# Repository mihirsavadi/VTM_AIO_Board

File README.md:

# All-in-One Board | Virginia Tech Motorsports

This repository contains all documentation and material related to [Virginia Tech's Formula SAE team - Virginia Tech Motorsports](https://vtmotorsports.weebly.com/) - All-in-One board for our 2021/2022 internal combustion vehicle.

The AIO board encapsulates several data acquisition features, as well as rules compliant power staging and power distribution, into a single PCB. Note that it is tightly integrated with our Brake-System-Plausibility device which can be found at the repository over [here](https://vtmotorsports.weebly.com/). 

The repository is split into [hardware](./hardware) and [software](./software) subdirectories. The former contains schematics, BOM, etc. Note that I used Diptrace as my PCB design software of choice, and while all critical files for board fabrication/inventory management are available in standard formats (GERBER, pdf's, spreadsheets), the original Diptrace files are included as well. The rest of the team uses Altium, however I prefer Diptrace - its easy to port between the two. The software directory contains Platform-IO project files that run both the MAIN and DRS microcontrollers on the AIO board. Custom Hardware Abstraction Layers/API's were made in order to make it easy to work with the board's slew of features. Both subdirectories include folders containing all our old revisions, which can be safely ignored unless you are a VTM member and/or are curious about the evolution of our design process.  

Running our microcontrollers with the Arduino bootloader and its general hardware abstraction layer not only allows us access to a vast array of arduino compatible easy-to-use libraries for various embedded hardware components (saving us dev time), but also allows lesser experienced team members to absorb functionality and hit the ground running with contribution quicker. We suffer from little to nothing when it comes to the typical drawbacks of using the arduino abstraction layer because 1. we are using proven and optimized hardware by standardizing to the teensy line of microcontrollers, 2. we are not using the stock arduino IDE, rather platform IO which is an extremely rich and ever-expanding IDE for a vast array of embedded processors and development boards, allowing us to easily and reliably integrate custom as well as off-the-shelf open source libraries, and 3. all of our applications are low speed and low memory.  

## Software Guide

Please read all the code in the /src directories for both the AIO_MAIN_MCU and AIO_DRS_MCU to understand the system thoroughly and before attempting to modify any code. All pin/IO definitions for the microcontrollers are established as macros in a file called "pin_definitions.hpp" in both directories, please study these and compare them with the schematics in the hardware subdirectories. Only use these macros for pin control in the code in order to keep things consistent, clean, and less error prone. Also remember to see header comments in order to match code and hardware compatibility - everything in the top level directories by default should be compatible with the latest hardware revision, which as of writing this is 'DAQ_PDU AIO BOARD REV2'.

In order to get an idea of how to use the various libraries to interact with peripherals on the AIO (SD card, GPS, IMU), read the documentation and example arduino sketches in the lib_dep directory. So for the MAIN MCU this would be [.pio\libdeps\teensy35](./software/AIO_MAIN_MCU/.pio/libdeps/teensy35)

If you want to add libraries, please visit the Platform-IO libraries registry and add the dependency into our project's 'platformio.ini' file. [This video](https://www.youtube.com/watch?v=buFKeqbafDI) illustrates this nicely. This file basically configures every option about our project - the serial port baud rate, library dependencies, what board etc were using, everything. Its a very powerful tool.  

Note that the arduino hardware abstraction layer compiles C++, but in reality most things are in C. The only significant usable C++ features are classes. Absolutely nothing from the C++ standard library should be used as it will wreck your boards memory and probably cause stack fragmentation which will either brick or freeze your board, which will be hard to debug. You can get away with using an std::string or an std::vector here or there but since its such a nasty slippery slope that hits quick stay away from it at all costs. So if you want to use convenient C++ like data structures (besides classes or structs) I recommend you don't. If you feel like you really must then its a sign your code is probably a tad too complicated for a simple embedded application such as ours - it might even mean you may be compromising on execution speed, which is bad given the primary purpose of software in this system being for data logging. [This](https://apprize.best/programming/arduino/10.html) is a nice resource regarding arduino programming and data structures.

I've tried my best to comment as much as possible, but if you have any questions reach out to me at mihirsavadi1@vt.edu.

## TODOS and Notes

- Add more pictures of the board to this readme, assembled as well as in enclosure (include wire jumps on the back)
- Implement BB method in DRS MCU class
- Implement IMU and GPS integration into the [aioMainMCU class](software/AIO_MAIN_MCU/src/aioMainMCU.cpp) (*integrated, not yet tested in hardware)
- Use RTC in GPS to get time data and add as a data point to CSV logging - IMPORTANT!
- Implement UART comms between DRS and MAIN MCU's
- Sort out CANBUS in MAIN MCU
- Clean up old revision subdirectories with information regarding what went wrong with them
- Include links to lecture videos describing entire system that we made (to youtube or something)
- Include wire map information here when that is all finalized and hashed out. 
- Add the CAD models for the AIO enclosure + BOM. Add a little window for a tiny fan for cooling, embedded flush into the enclosure.
- Add link to AIO breakdown documentation video

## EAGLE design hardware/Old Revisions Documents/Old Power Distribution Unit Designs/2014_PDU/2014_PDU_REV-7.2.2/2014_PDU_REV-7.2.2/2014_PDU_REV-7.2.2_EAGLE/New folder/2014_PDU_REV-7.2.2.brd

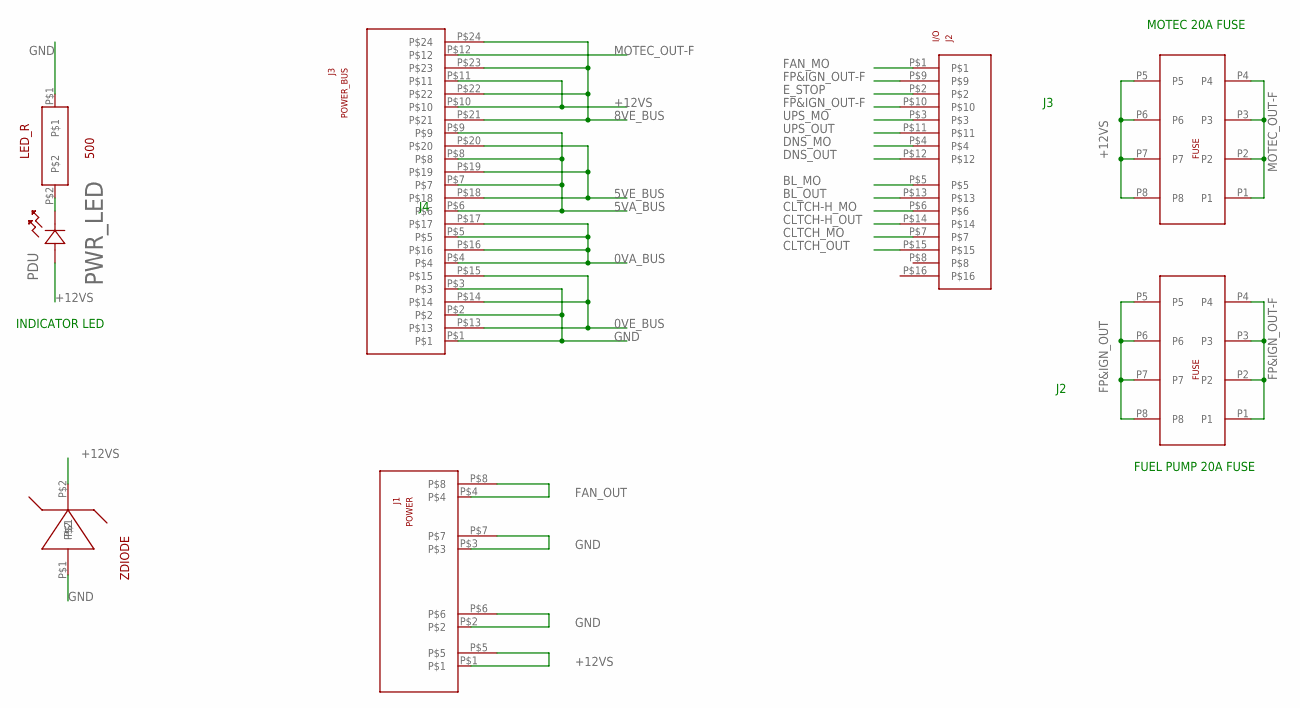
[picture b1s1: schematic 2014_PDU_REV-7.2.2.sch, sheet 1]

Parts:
I/O: J2; 39-30-1160
LED_R: 500; CRCW_2010_390R_JNEF
PDU: PWR_LED; LED_597-3111-407F
POWER: J1; 42820-4223
POWER_BUS: J3; 39-30-1240
U$1, U$2: 178.6165.0002
ZDIODE: DDZ20C-7

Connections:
0VA_BUS: POWER_BUS.P$4, POWER_BUS.P$5, POWER_BUS.P$16, POWER_BUS.P$17
0VE_BUS: POWER_BUS.P$13, POWER_BUS.P$14, POWER_BUS.P$15
5VA_BUS: POWER_BUS.P$6, POWER_BUS.P$7, POWER_BUS.P$8, POWER_BUS.P$9
5VE_BUS: POWER_BUS.P$18, POWER_BUS.P$19, POWER_BUS.P$20
8VE_BUS: POWER_BUS.P$21, POWER_BUS.P$22, POWER_BUS.P$23, POWER_BUS.P$24
+12VS: PDU.2, POWER.P$1, POWER.P$5, POWER_BUS.P$10, POWER_BUS.P$11, U$1.P5, U$1.P6, U$1.P7, U$1.P8, ZDIODE.P$2; also elsewhere on the board
BL_MO: I/O.P$5; also elsewhere on the board
BL_OUT: I/O.P$13; also elsewhere on the board
CLTCH-H_MO: I/O.P$6; also elsewhere on the board
CLTCH-H_OUT: I/O.P$14; also elsewhere on the board
CLTCH_MO: I/O.P$7; also elsewhere on the board
CLTCH_OUT: I/O.P$15; also elsewhere on the board
DNS_MO: I/O.P$4; also elsewhere on the board
DNS_OUT: I/O.P$12; also elsewhere on the board
E_STOP: I/O.P$2; also elsewhere on the board
FAN_MO: I/O.P$1; also elsewhere on the board
FAN_OUT: POWER.P$4, POWER.P$8; also elsewhere on the board
FP&IGN_OUT: U$2.P5, U$2.P6, U$2.P7, U$2.P8; also elsewhere on the board
FP&IGN_OUT-F: I/O.P$9, I/O.P$10, U$2.P1, U$2.P2, U$2.P3, U$2.P4
GND: LED_R.P$1, POWER.P$2, POWER.P$3, POWER.P$6, POWER.P$7, POWER_BUS.P$1, POWER_BUS.P$2, POWER_BUS.P$3, ZDIODE.P$1; also elsewhere on the board
MOTEC_OUT-F: POWER_BUS.P$12, U$1.P1, U$1.P2, U$1.P3, U$1.P4
unnamed: LED_R.P$2, PDU.1
UPS_MO: I/O.P$3; also elsewhere on the board
UPS_OUT: I/O.P$11; also elsewhere on the board

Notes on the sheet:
INDICATOR LED
MOTEC 20A FUSE
FUEL PUMP 20A FUSE

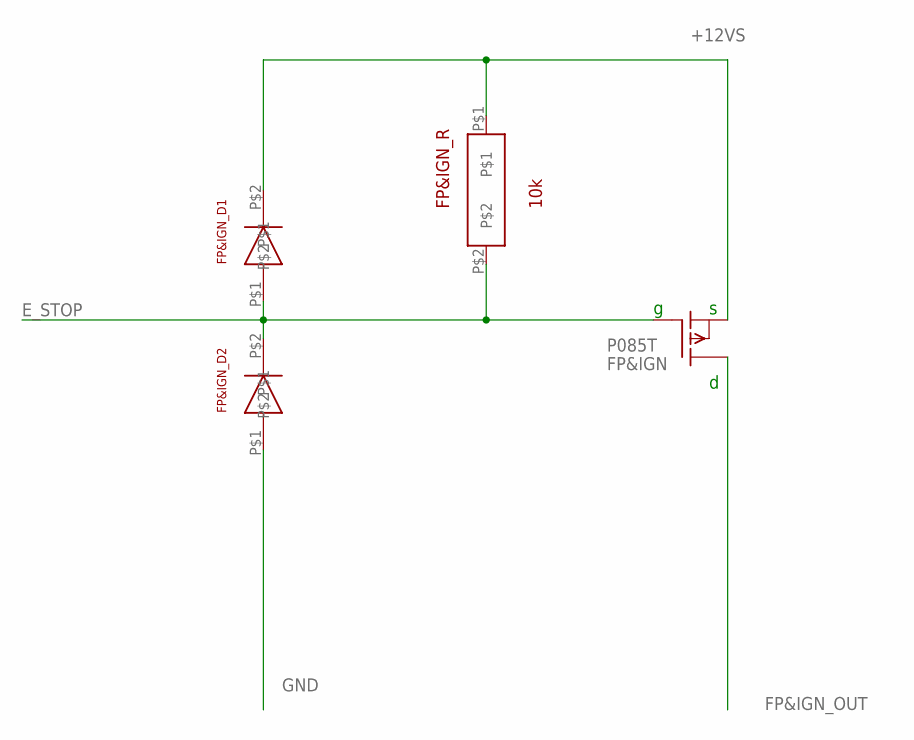
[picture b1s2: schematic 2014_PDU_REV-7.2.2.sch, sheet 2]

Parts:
FP&IGN: P085T; TO220
FP&IGN_D1, FP&IGN_D2: ER3JB-TP
FP&IGN_R: 10k; CRCW_2010_10K0_JNEF

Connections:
+12VS: FP&IGN.3 (S), FP&IGN_D1.P$2, FP&IGN_R.P$1; also elsewhere on the board
E_STOP: FP&IGN.1 (G), FP&IGN_D1.P$1, FP&IGN_D2.P$2, FP&IGN_R.P$2; also elsewhere on the board
FP&IGN_OUT: FP&IGN.2 (D); also elsewhere on the board
GND: FP&IGN_D2.P$1; also elsewhere on the board

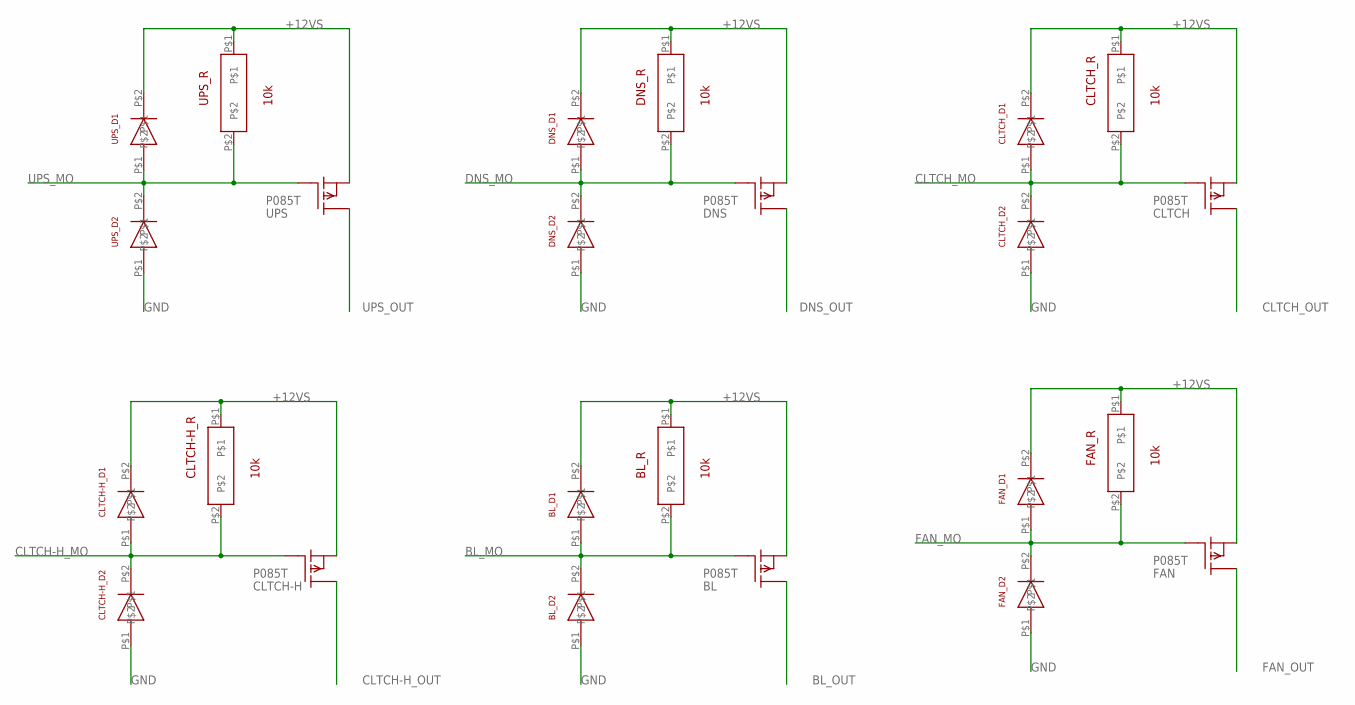
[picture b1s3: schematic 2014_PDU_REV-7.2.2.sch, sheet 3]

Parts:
BL: P085T; TO220
BL_D1, BL_D2: ER3JB-TP
BL_R: 10k; CRCW_2010_10K0_JNEF
CLTCH: P085T; TO220
CLTCH-H: P085T; TO220
CLTCH-H_D1, CLTCH-H_D2: ER3JB-TP
CLTCH-H_R: 10k; CRCW_2010_10K0_JNEF
CLTCH_D1, CLTCH_D2: ER3JB-TP
CLTCH_R: 10k; CRCW_2010_10K0_JNEF
DNS: P085T; TO220
DNS_D1, DNS_D2: ER3JB-TP
DNS_R: 10k; CRCW_2010_10K0_JNEF
FAN: P085T; TO220
FAN_D1, FAN_D2: ER3JB-TP
FAN_R: 10k; CRCW_2010_10K0_JNEF
UPS: P085T; TO220
UPS_D1, UPS_D2: ER3JB-TP
UPS_R: 10k; CRCW_2010_10K0_JNEF

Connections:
+12VS: BL.3 (S), BL_D1.P$2, BL_R.P$1, CLTCH.3 (S), CLTCH-H.3 (S), CLTCH-H_D1.P$2, CLTCH-H_R.P$1, CLTCH_D1.P$2, CLTCH_R.P$1, DNS.3 (S), DNS_D1.P$2, DNS_R.P$1, FAN.3 (S), FAN_D1.P$2, FAN_R.P$1, UPS.3 (S), UPS_D1.P$2, UPS_R.P$1; also elsewhere on the board
BL_MO: BL.1 (G), BL_D1.P$1, BL_D2.P$2, BL_R.P$2; also elsewhere on the board
BL_OUT: BL.2 (D); also elsewhere on the board
CLTCH-H_MO: CLTCH-H.1 (G), CLTCH-H_D1.P$1, CLTCH-H_D2.P$2, CLTCH-H_R.P$2; also elsewhere on the board
CLTCH-H_OUT: CLTCH-H.2 (D); also elsewhere on the board
CLTCH_MO: CLTCH.1 (G), CLTCH_D1.P$1, CLTCH_D2.P$2, CLTCH_R.P$2; also elsewhere on the board
CLTCH_OUT: CLTCH.2 (D); also elsewhere on the board
DNS_MO: DNS.1 (G), DNS_D1.P$1, DNS_D2.P$2, DNS_R.P$2; also elsewhere on the board
DNS_OUT: DNS.2 (D); also elsewhere on the board
FAN_MO: FAN.1 (G), FAN_D1.P$1, FAN_D2.P$2, FAN_R.P$2; also elsewhere on the board
FAN_OUT: FAN.2 (D); also elsewhere on the board
GND: BL_D2.P$1, CLTCH-H_D2.P$1, CLTCH_D2.P$1, DNS_D2.P$1, FAN_D2.P$1, UPS_D2.P$1; also elsewhere on the board
UPS_MO: UPS.1 (G), UPS_D1.P$1, UPS_D2.P$2, UPS_R.P$2; also elsewhere on the board
UPS_OUT: UPS.2 (D); also elsewhere on the board

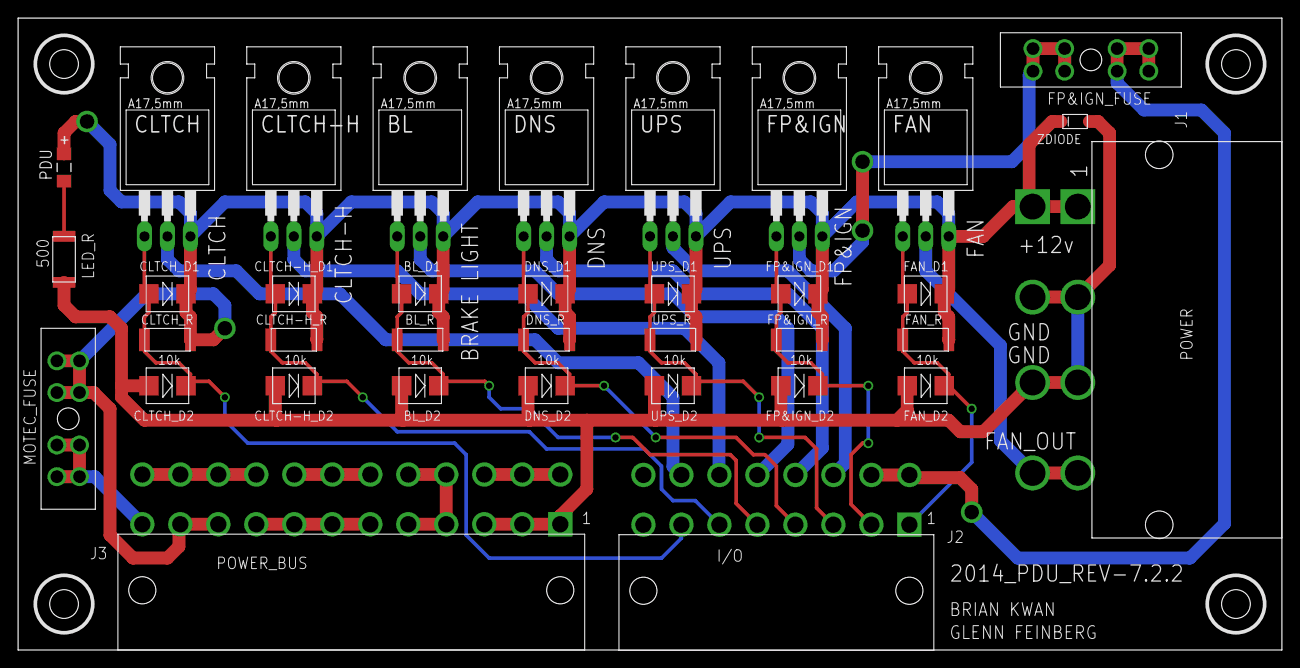
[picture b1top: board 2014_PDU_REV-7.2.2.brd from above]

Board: 2 copper layers, 139.7 x 69.8 mm, 36 parts (0 on the bottom side), 24 nets.

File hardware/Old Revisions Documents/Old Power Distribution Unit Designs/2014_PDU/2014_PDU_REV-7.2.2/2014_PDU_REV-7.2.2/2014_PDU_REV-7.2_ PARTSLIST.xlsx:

Created By | Brian Kwan |  |  |  | Parts List
Checked By
Date | 41686
 |  |  |  |  | Name | 2014_PDU
 |  |  |  |  | Rev | 6.2
item Number | Part Number |  | Part Name |  |  | Quantity | Unit of Measure |  | Ref | Notes |  |  | Need for 3 Boards
1 | ER3JB-TP |  | Diode, Surface Mount |  |  | 14 | each |  |  |  |  |  | 45 |  | YOU NEED TO FIND AND ORDER THE MATE TO THE POWER CONNECTOR, ITEM 9 AS WELL
2 | IXTP24P085T |  | MOSFET, P-Channel, Thru Hole |  |  | 7 | each |  |  |  |  |  | 24
3 | CRCW201010K0JNEF |  | Resistor, 10k, SMD |  |  | 7 | each |  |  |  |  |  | 24
4 | CRCW2010499RFKEFHP |  | Resistor, 500, SMD |  |  | 1 | each |  |  |  |  |  | 3
5 |  |  |  |  |  |  |  |  |  |  |  |  | 0
6 | DDZ20C-7 |  | Diode, Zener, 20V |  |  | 1 | each |  |  | Purchase from Digikey |  |  | 3
7 | 597-6001-607F |  | LED, SMD, RED |  |  | 1 | each |  |  |  |  |  | 3
8 | 4724 |  | TO-220 Mounting Hardware |  |  | 8 | each |  |  | Insulator, screw, rubber washer, nut, washer |  |  | 24
9 | 42820-4223 |  | Molex Board Power Connector |  |  | 1 | each |  |  | Buy from Mouser |  |  | 4
10 | 42816-0412 |  | Molex 4 Pin Power Receptacle |  |  | 1 | each |  |  | Buy from Mouser, mates with Item 10 |  |  | 4
11 | 39-30-1160 |  | Molex Board Connector, 16 POS |  |  | 1 | each |  |  |  |  |  | 4
12 | 39-30-1240 |  | Molex Board Connector, 24 POS |  |  | 1 | each |  |  |  |  |  | 4
 |  |  |  |  |  |  |  |  |  |  |  |  | 0
14 | 39-01-2160 |  | Molex Connector, 16 POS Recp |  |  | 1 | each |  |  | Mates with Item 11 |  |  | 3
15 | 39012240 |  | Molex Connector, 24 POS Recp |  |  | 1 | each |  |  | Mates with Item 12 |  |  | 4
16 | 178.6165.0002 |  | Fuse Holder |  |  | 2 | each |  |  |  |  |  | 6
 |  |  | Fuses, 20 Amps |  |  | 2 | each |  |  | Use with item 16 |  |  | 6

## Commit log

2021-04-18 added another improvement point
2021-04-18 neutral spelling typo
2021-04-18 made class skeleton
2021-04-18 added comments
2021-04-18 fixed broken link
2021-04-18 implemented most of main mcu code. logging method remaining
2021-04-18 finished sd card writing code
2021-04-18 updated todos
2021-04-18 added some sugar to main
2021-04-18 typos
2021-04-18 added macro controls
2021-04-18 changed project and build flags to make sure fast as shit
2021-04-18 added pictures
2021-04-18 added comments to top of file
2021-04-18 added todo
2021-04-18 added more todos and gps imu functionality skeletons
2021-04-18 added pio build flags and settings to set at fastest speed
2021-04-18 early DRS class skeleton
2021-04-18 added NKK M2028TJW01-GA-1A - the brake bias toggle switch that the DRS MCU is built around - to the BOM
2021-04-18 improved on logAllInputs() logging verbosity
2021-04-19 README.md
2021-04-19 added rtc todo
2021-04-26 added to readme
2021-04-26 integrated gps rudimentarily no testing yet
2021-04-26 added first iteration of setup sd card column header print
2021-04-27 implemented GPS stuff rudimentary no testing yet
2021-04-27 implemented runDRSservo() method
2021-04-27 added an extra method and macro to make conversion of ADC values from current sensor to amps easy for logging. also added code to convert adc from voltage reads to volt units
2021-04-27 fixed silly rundrs errors
2021-04-27 added comment in header comments specifiying hardware revision
2021-04-27 turned on serial prints
2021-04-27 removed commas to fix csv stuff
2021-04-27 added point on servo fuse
2021-04-30 typo in helper function
2021-04-30 added a serial print helper function. also tested for current sensor offset constant by running starter motor in bay. Just subtracted average DC offset in idle from sensor reading. simple dimple.
2021-05-01 edited todos
2021-05-01 cleaned up some code, trivial bracket edits
2021-05-02 0805 resitor pattern mismatch
2021-05-03 changed sensor in bom from 150U to 050B
2021-05-03 more junk
2021-05-04 added more improvement points
2021-05-05 added method and functionality in aioDRSMCU class of manual control of servos through serial monitor for testing and wing mount setup
2021-05-05 set servo positions
2021-07-25 removed some superflousness and touched up readme details
2021-07-30 added improvement comment on differential pair signals
2021-07-30 added todo comment
2021-09-01 added new pics

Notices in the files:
README.md:
License: CC BY-NC-SA 4.0
